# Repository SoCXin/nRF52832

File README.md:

# [nRF52832](https://github.com/SoCXin/nRF52832) 

#### [Vendor](https://github.com/SoCXin/Vendor) ：[Nordic](https://github.com/SoCXin/Nordic) 
#### [Core](https://github.com/SoCXin/Cortex) ：[Cortex M4](https://github.com/SoCXin/CM4) 
#### [Level](https://github.com/SoCXin/Level) ：64MHz 

### [nRF52832简介](https://github.com/SoCXin/nRF52832/wiki)

[nRF52832](https://github.com/SoCXin/nRF52832) 是一款超低功耗多协议SoC，嵌入式2.4GHz收发器，支持BLE、ANT和2.4GHz超低功耗应用。

64 MHz的32位 ARM® Cortex™-M4F处理器，64 MHz主频，与竞争者的解决方案相比，提供多出60%的通用处理能力以及十倍浮点和两倍数字信号处理(DSP)性能。nRF52832器件的2.4 GHz多协议无线电完全兼容蓝牙4.2规范，并且具有-96 dB RX 灵敏度和5.5 mA 峰值RX/TX电流。nRF52832 还具有512 kB Flash和64 kB RAM，有400KB的Flash可用于放置开发应用程序，以及优化的全自动功耗管理系统。

nRF52832芯片支持NFC-A，可以作为NFC Tag使用，包括了AES硬件加密，12位ADC，可在1.7V - 3.6V的电源电压下工作。

相比前代产品nRF51822功耗几乎降低了一半，有接近-96dBm的射频接收灵敏度,-30dBm — 4dBm的宽幅输出功率调节。

### [资源收录](https://github.com/SoCXin)

* [文档](docs/)
* [资源](src/)

### [关联资源](https://github.com/SoCXin)

* [开源项目](https://github.com/NordicSemiconductor)
* [官方SDK](https://www.nordicsemi.com/Software-and-Tools/Software/nRF5-SDK)
* [platformIO](https://platformio.org/platforms/nordicnrf52)

#### [硬件设计资源](https://github.com/SoCXin/nRF52832)

封装：QFN48 (QFAA 6mm x 6mm) 

### [开源项目](https://github.com/SoCXin)

* [nrf52832-mdk](https://github.com/makerdiary/nrf52832-mdk)
* [RT-Thread](https://github.com/Zero-Free/nrf52832-nimble)
* [nRF52832开发指南](https://github.com/HX-IoT/nRF52832-Developer-Guide)

### [选型建议](https://github.com/SoCXin)

[nRF52832](https://github.com/SoCXin/nRF52832)是一款性能非常强大的明星BLE SoC产品，芯片综合实力强大，网络参考资源非常丰富，非常适合应用于原型开发，特别是对NFC tag有需求的产品。同系列更高规格产品还有[nRF52833](https://github.com/SoCXin/nRF52833)、[nRF52840](https://github.com/SoCXin/nRF52840)

[nRF52832](https://github.com/SoCXin/nRF52832)的市场竞争对手为TI SimpleLink系列的[CC2640](https://github.com/SoCXin/CC2640)，Nordic的产品相比TI产品在开发工具和资源策略上不同，Nordic产品的性能更强但TI的低功耗更好。

###  [SoC芯平台](http://SoC.Xin)

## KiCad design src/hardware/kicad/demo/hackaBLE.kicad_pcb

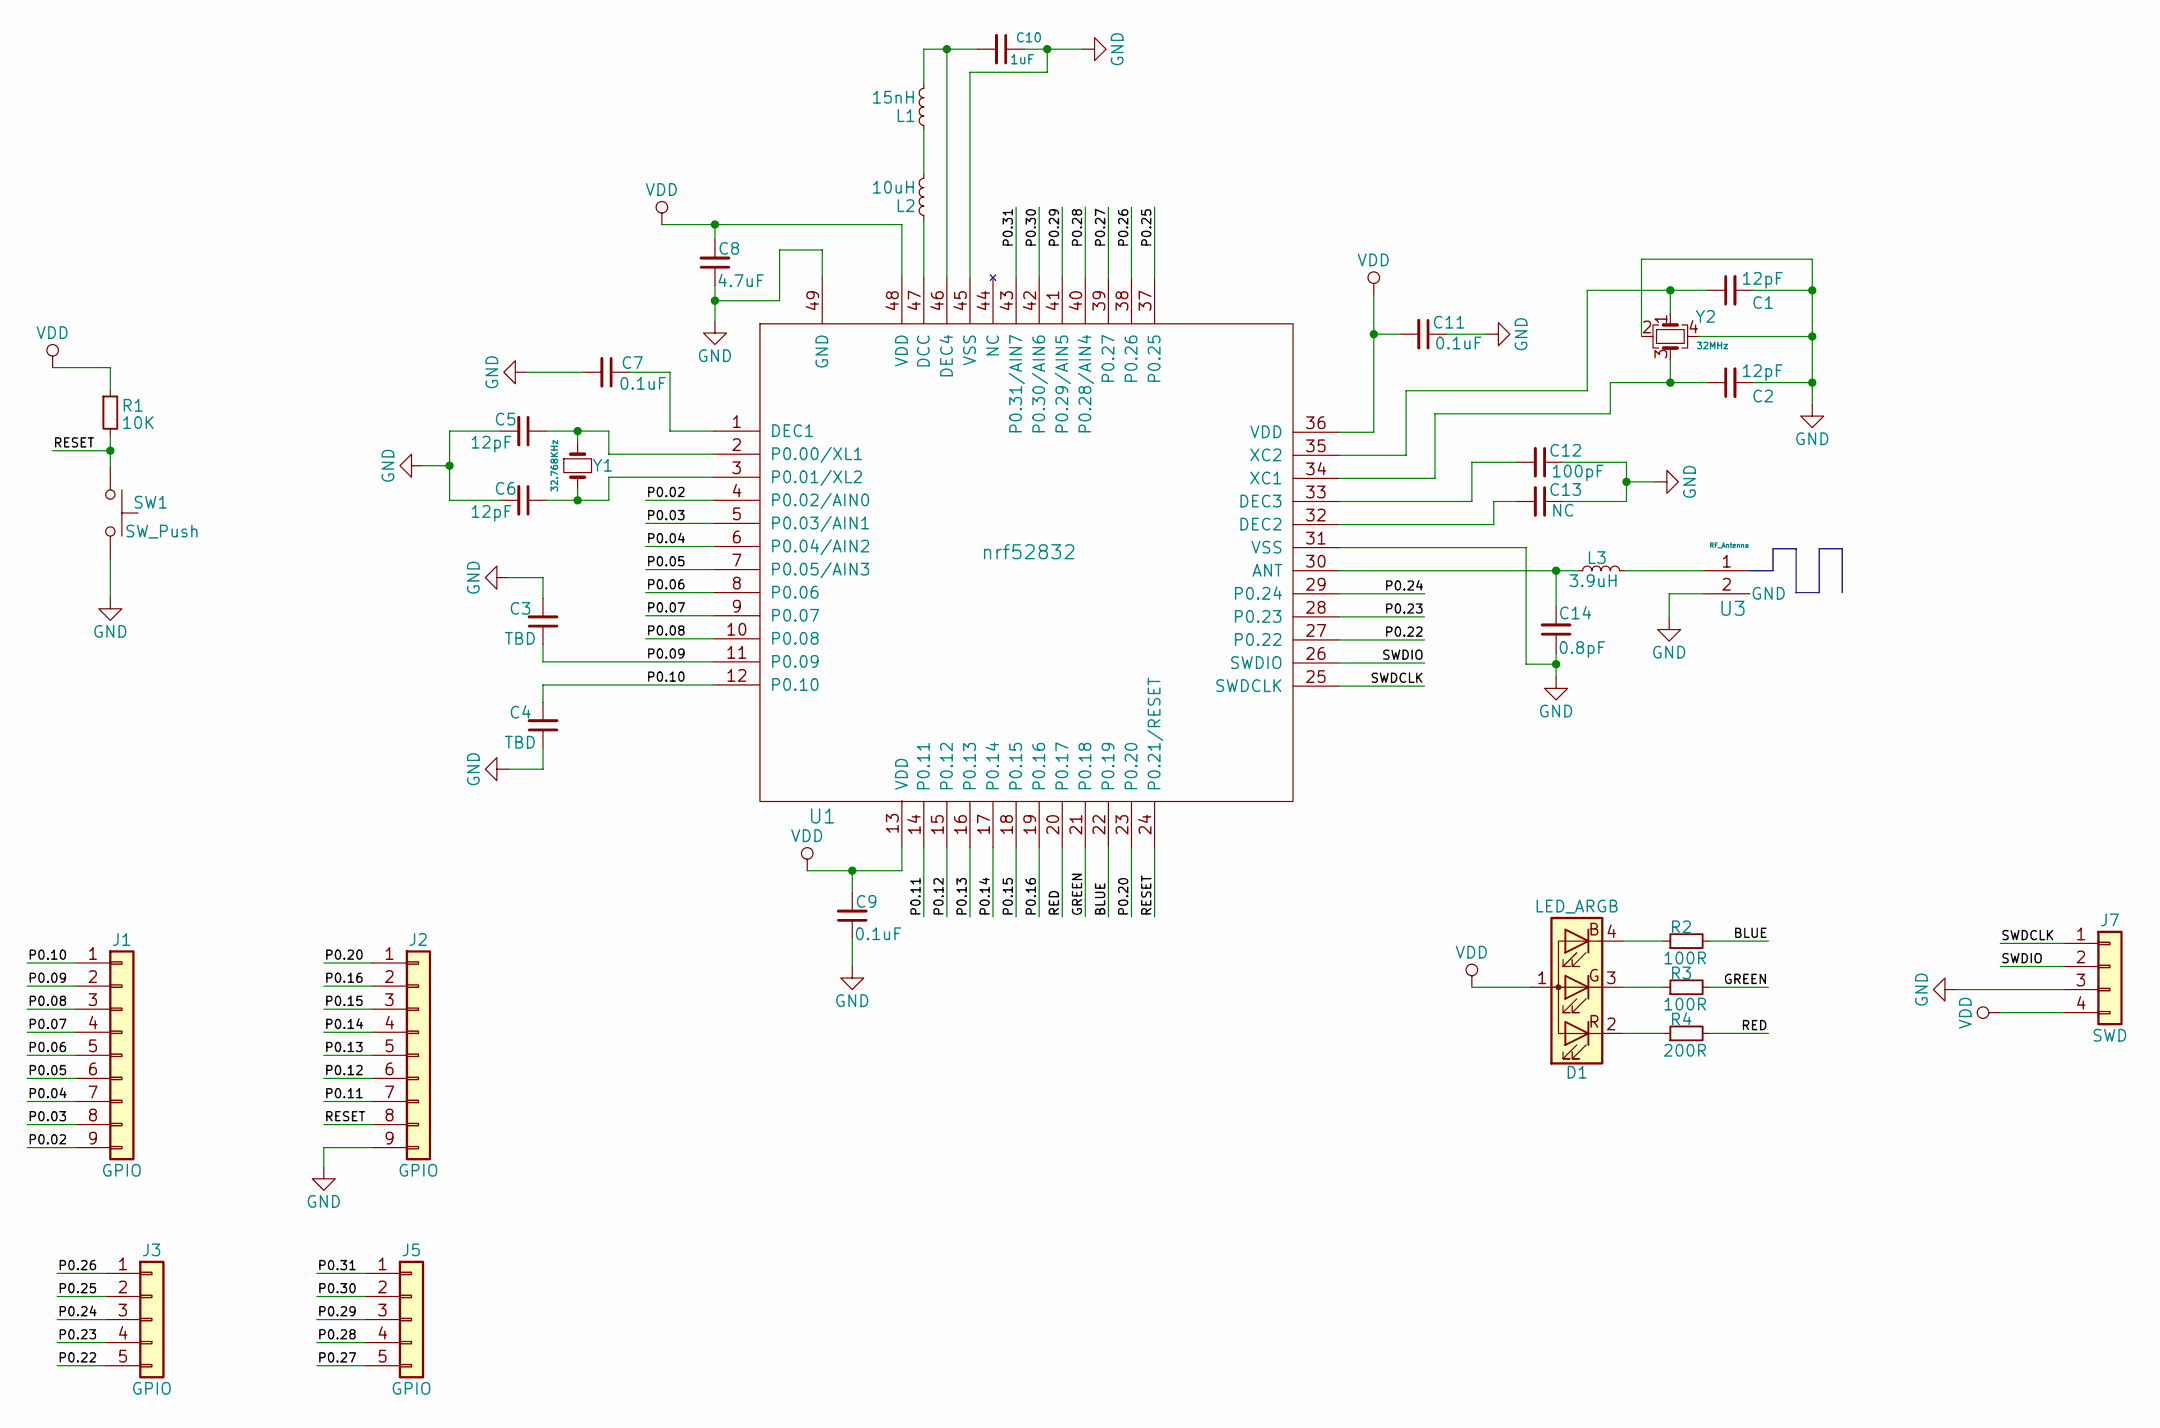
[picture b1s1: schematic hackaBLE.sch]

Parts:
C1, C2, C5, C6: 12pF; C_0402
C3, C4: TBD; C_0603
C7, C9, C11: 0.1uF; C_0402
C8: 4.7uF; C_0603
C10: 1uF; C_0603
C12: 100pF; C_0402
C13: NC; C_0402
C14: 0.8pF; SMD_0402
D1: LED_ARGB; RGB_LED
J1, J2: GPIO; PinHeaderStraight1x09_Pitch2.54mm
J3, J5: GPIO; 5pin_header
J7: SWD; Pin_Header_Straight_1x05_Pitch2.54mm
L1: 15nH; C_0402
L2: 10uH; Neosid_Inductor_SM0603CG
L3: 3.9uH; SMD_0402
R1: 10K; R_0603
R2, R3: 100R; R_0603
R4: 200R; R_0603
SW1: SW_Push; PTS810_Switch
U1: nrf52832; nRF52832
U3: RF_Antenna; Antenna-2.45GHZ_mirror
Y1: 32.768KHz; ABS07_crystal
Y2: 32MHz; 32MHz_crystal

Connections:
/BLUE: R2.2, U1.22 (P0.19)
/GREEN: R3.2, U1.21 (P0.18)
/P0.02: J1.9, U1.4 (P0.02/AIN0)
/P0.03: J1.8, U1.5 (P0.03/AIN1)
/P0.04: J1.7, U1.6 (P0.04/AIN2)
/P0.05: J1.6, U1.7 (P0.05/AIN3)
/P0.06: J1.5, U1.8 (P0.06)
/P0.07: J1.4, U1.9 (P0.07)
/P0.08: J1.3, U1.10 (P0.08)
/P0.09: C3.1, J1.2, U1.11 (P0.09)
/P0.10: C4.2, J1.1, U1.12 (P0.10)
/P0.11: J2.7, U1.14 (P0.11)
/P0.12: J2.6, U1.15 (P0.12)
/P0.13: J2.5, U1.16 (P0.13)
/P0.14: J2.4, U1.17 (P0.14)
/P0.15: J2.3, U1.18 (P0.15)
/P0.16: J2.2, U1.19 (P0.16)
/P0.20: J2.1, U1.23 (P0.20)
/P0.22: J3.5, U1.27 (P0.22)
/P0.23: J3.4, U1.28 (P0.23)
/P0.24: J3.3, U1.29 (P0.24)
/P0.25: J3.2, U1.37 (P0.25)
/P0.26: J3.1, U1.38 (P0.26)
/P0.27: J5.5, U1.39 (P0.27)
/P0.28: J5.4, U1.40 (P0.28/AIN4)
/P0.29: J5.3, U1.41 (P0.29/AIN5)
/P0.30: J5.2, U1.42 (P0.30/AIN6)
/P0.31: J5.1, U1.43 (P0.31/AIN7)
/RED: R4.2, U1.20 (P0.17)
/RESET: J2.8, R1.2, SW1.1, U1.24 (P0.21/RESET)
/SWDCLK: J7.1, U1.25 (SWDCLK)
/SWDIO: J7.2, U1.26 (SWDIO)
GND: C1.2, C2.2, C3.2, C4.1, C5.2, C6.2, C7.2, C8.1, C9.1, C10.1, C11.1, C12.1, C13.1, C14.1, J2.9, J7.3, SW1.2, U1.31 (VSS), U1.45 (VSS), U1.49 (GND), U3.2 (GND), Y2.2, Y2.4
unnamed: C1.1, U1.35 (XC2), Y2.1
unnamed: C2.1, U1.34 (XC1), Y2.3
unnamed: C5.1, U1.2 (P0.00/XL1), Y1.1
unnamed: C6.1, U1.3 (P0.01/XL2), Y1.2
unnamed: C7.1, U1.1 (DEC1)
unnamed: C10.2, L1.2, U1.46 (DEC4)
unnamed: C12.2, U1.33 (DEC3)
unnamed: C13.2, U1.32 (DEC2)
unnamed: C14.2, L3.1, U1.30 (ANT)
unnamed: D1.2 (RK), R4.1
unnamed: D1.3 (GK), R3.1
unnamed: D1.4 (BK), R2.1
unnamed: L1.1, L2.2
unnamed: L2.1, U1.47 (DCC)
unnamed: L3.2, U3.1
VDD: C8.2, C9.2, C11.2, D1.1 (A), J7.4, R1.1, U1.13 (VDD), U1.36 (VDD), U1.48 (VDD)

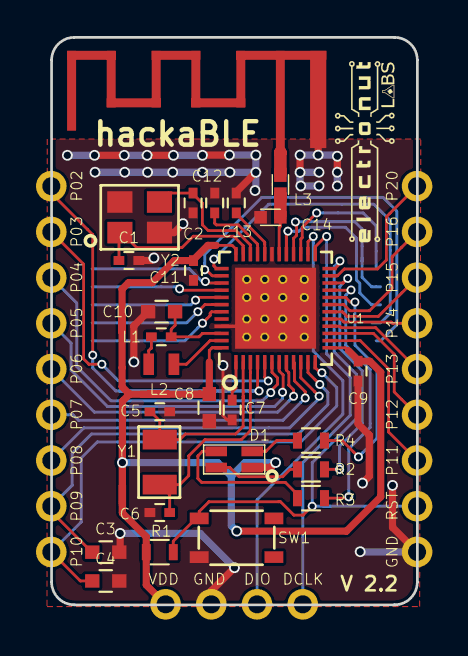
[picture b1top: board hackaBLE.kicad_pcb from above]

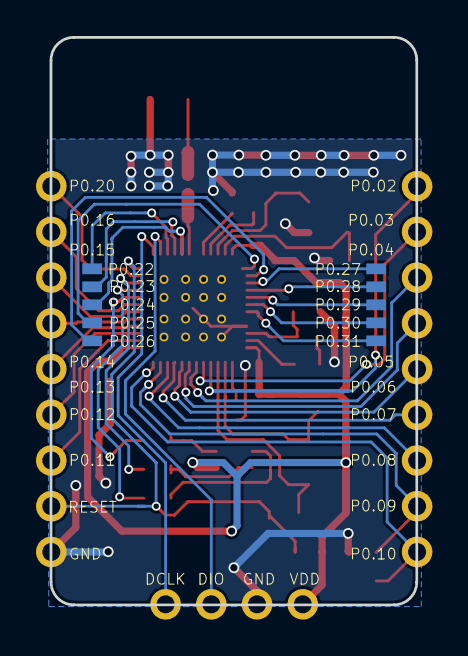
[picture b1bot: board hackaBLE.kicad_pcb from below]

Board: 2 copper layers, 20.3 x 31.5 mm, 32 parts (2 on the bottom side), 49 nets.

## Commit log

2018-11-22 add project
2018-12-01 add more src
2018-12-06 fix project
2019-04-29 fix init
2019-05-20 fix repo
2019-05-20 add pre
2019-05-20 add kicad
2019-05-20 add demo
2019-05-21 add src
2019-05-24 fix repo src
2019-05-24 fix add bootloader
2019-07-03 fix add project
2019-08-18 add gitgnore
2019-08-18 new name
2020-05-01 fix more
2020-05-01 fix more
